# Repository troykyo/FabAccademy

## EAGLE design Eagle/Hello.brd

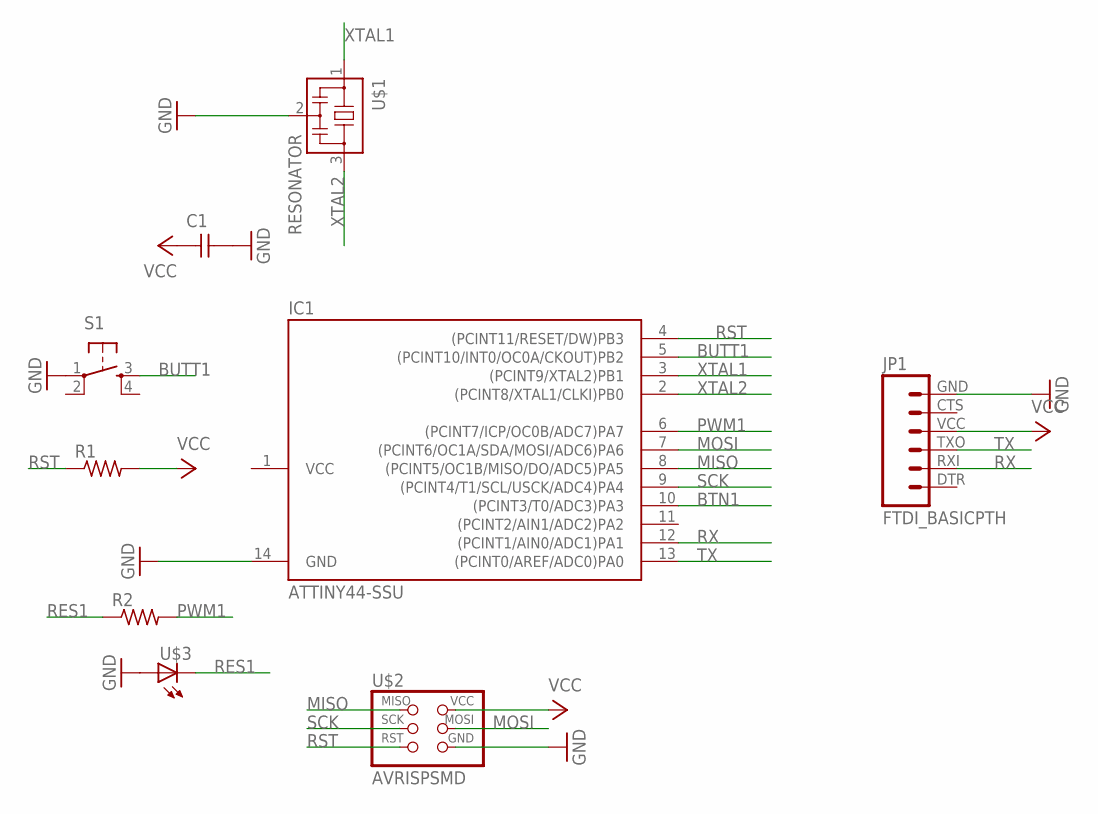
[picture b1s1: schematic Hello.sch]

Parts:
C1: UNPOLARIZED_CAPACITOR1206; 1206
IC1: ATTINY44-SSU; SOIC14
JP1: FTDI_BASICPTH; FTDI_BASIC
R1, R2: RESISTOR1206; 1206
S1: 6MM_SWITCH6MM_SWITCH; 6MM_SWITCH
U$1: RESONATOR; EFOBM
U$2: AVRISPSMD; 2X03SMD
U$3: LED1206; 1206

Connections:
BTN1: IC1.10 ((PCINT3/T0/ADC3)PA3)
BUTT1: IC1.5 ((PCINT10/INT0/OC0A/CKOUT)PB2), S1.3 (S)
GND: C1.2, IC1.14 (GND), JP1.GND (6), S1.1, U$1.2, U$2.6 (GND), U$3.1 (A)
MISO: IC1.8 ((PCINT5/OC1B/MISO/DO/ADC5)PA5), U$2.1 (MISO)
MOSI: IC1.7 ((PCINT6/OC1A/SDA/MOSI/ADC6)PA6), U$2.4 (MOSI)
PWM1: IC1.6 ((PCINT7/ICP/OC0B/ADC7)PA7), R2.2
RES1: R2.1, U$3.2 (C)
RST: IC1.4 ((PCINT11/RESET/DW)PB3), R1.1, U$2.5 (RST)
RX: IC1.12 ((PCINT1/AIN0/ADC1)PA1), JP1.RXI (2)
SCK: IC1.9 ((PCINT4/T1/SCL/USCK/ADC4)PA4), U$2.3 (SCK)
TX: IC1.13 ((PCINT0/AREF/ADC0)PA0), JP1.TXO (3)
VCC: C1.1, IC1.1 (VCC), JP1.VCC (4), R1.2, U$2.2 (VCC)
XTAL1: IC1.3 ((PCINT9/XTAL2)PB1), U$1.1
XTAL2: IC1.2 ((PCINT8/XTAL1/CLKI)PB0), U$1.3

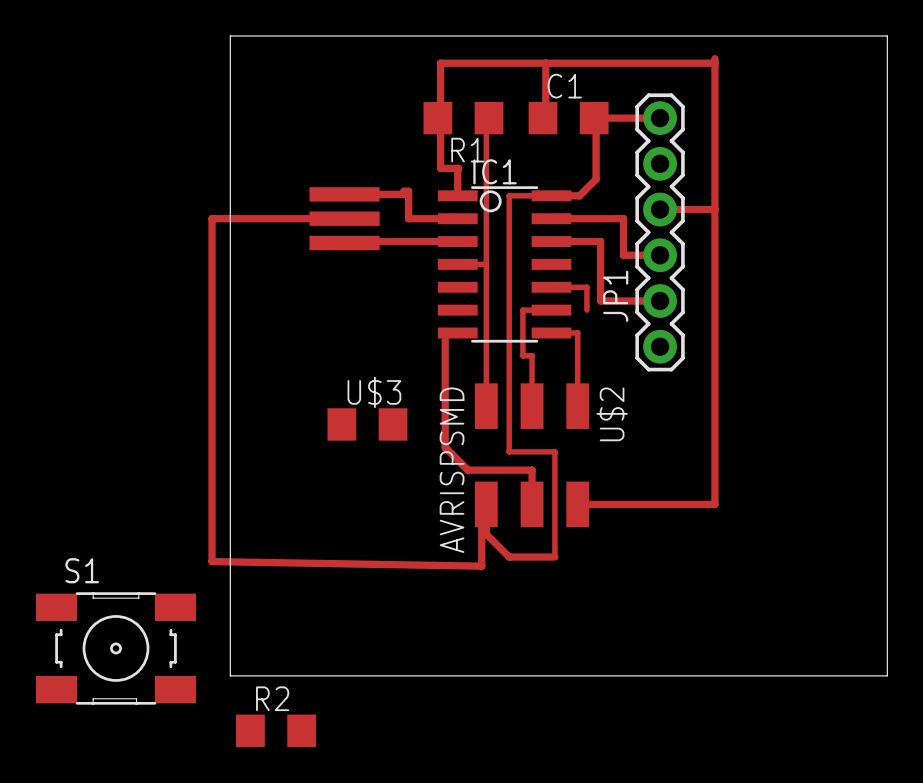
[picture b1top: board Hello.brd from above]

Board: 2 copper layers, 36.5 x 35.5 mm, 9 parts (0 on the bottom side), 13 nets.

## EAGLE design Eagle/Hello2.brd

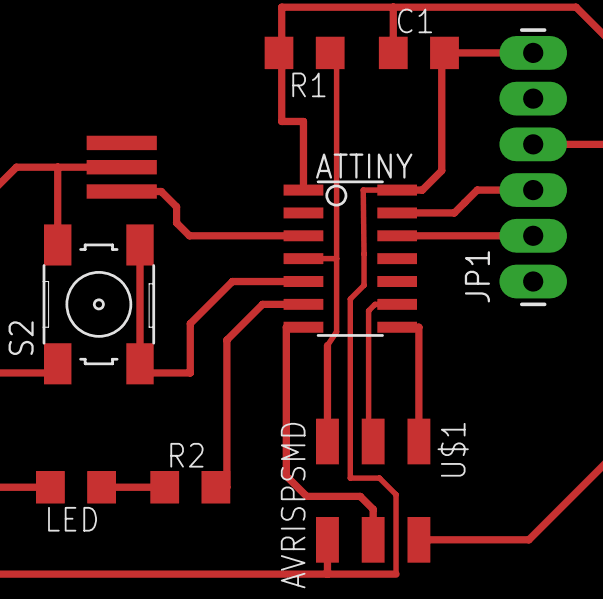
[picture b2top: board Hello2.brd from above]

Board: 2 copper layers, 9 parts (0 on the bottom side), 12 nets.

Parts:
ATTINY: ATTINY44-SSU; SOIC14
C1: 1206
JP1: 1X06_LONGPADS
LED: 1206
QUARTZ: RESONATOR; EFOBM
R1, R2: 1206
S2: 6MM_SWITCH
U$1: AVRISPSMD; 2X03SMD

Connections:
BUT: ATTINY.5, S2.3, S2.4
GND: ATTINY.14, C1.2, JP1.6, LED.2, QUARTZ.2, S2.1, S2.2, U$1.6
LED: ATTINY.6, R2.2
LEDRES: LED.1, R2.1
MISO: ATTINY.8, U$1.1
MOSI: ATTINY.7, U$1.4
RST: ATTINY.4, R1.1, U$1.5
RX: ATTINY.12, JP1.2
SCK: ATTINY.9, U$1.3
TX: ATTINY.13, JP1.3
VCC: ATTINY.1, C1.1, JP1.4, R1.2, U$1.2
XTAL2: ATTINY.3, QUARTZ.1

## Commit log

2015-02-08 Development Archive
2015-05-12 big dump
2015-05-15 16 hour days

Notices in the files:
parts and their libraries:
SparkFun-Connectors: Licensing: Creative Commons ShareAlike 4.0 International - https://creativecommons.org/licenses/by-sa/4.0
